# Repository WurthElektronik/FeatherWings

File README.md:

# WE Adafruit FeatherWings

[Würth Elektronik eiSos](https://www.we-online.de/web/en/wuerth_elektronik/start.php) presents, a range of FeatherWing development boards that are **open source** and **fully compatible** with the **Feather form factor**. Through these development boards WE brings a range of wireless connectivity modules, sensors and power modules to the Feather ecosystem.

[Adafruit Feather](https://www.adafruit.com/feather) is a complete line of development boards from [Adafruit](https://www.adafruit.com/) and other developers that are both standalone and stackable. They're able to be powered by [LiPo batteries](https://en.wikipedia.org/wiki/Lithium_polymer_battery) for on-the-go use or by their [micro-USB](https://www.we-online.de/katalog/de/em/connectors/input_output_connectors/wr-com) or their [USB-C](https://www.we-online.com/de/components/products/WR-COM_USB_20_TYPE_C_RECEPTACLE_HORIZONTAL_SMT) plugs for line-powered projects. Feathers are flexible, portable, and as light as their namesake.

[FeatherWings](https://learn.adafruit.com/adafruit-feather/featherwings) are stacking boards and add functionality and room for prototyping. At its core, the Adafruit Feather is a complete ecosystem of products - and the best way to get your project flying.

Supercharge your prototyping for easy and fast solution testing.
Start by checking our [quick start section](#Quick-start-guide).

| Image    | Description |
| -------- | ----------- |
| | [**Proteus-III BLE FeatherWing** (not available as a standalone product)](/Setebos-I_FeatherWing/)<ul><li>Bluetooth® Low Energy 5.1 module<li>Nano SIM size<li>2 MBit PHY and Coded PHY (long range)<li>Connect to any smart device with an app. <br/> <br/> Note: this Feather is replaced by Setebos-I Feather with selectable radio protocol (either Proteus-III Bluetooth LE or Thyone-I)</ul> |
| | [**Adrastea-I FeatherWing** (2615039336001)](/AdrasteaFeatherWing) <ul> <li>LTE-Cat.M/LTE-Cat.NB-IoT<li>AIntegrated GNSS<li>Integrated User MCU<li>Secure IoT Connectivity using MQTT, LWM2M<br/> Note: This board can be used as a featherWing or as a standalone Feather.</ul> |
| | [**Sensor FeatherWing** (2501000201291)](/SensorFeatherWing) <ul> <li>Acceleration (WSEN-ITDS)<li>Absolute Pressure (WSEN-PADS)<li>Temperature (WSEN-TIDS)<li>Humidity (WSEN-HIDS)<li>[Sparkfun QWIIC® Connect System](https://www.sparkfun.com/qwiic) to connect additional peripherals <br/> <br/> Note: this FeatherWing will be updated with new sensors in the future.</ul> |
| | [**Calypso WiFi FeatherWing** (2610039025001)](/CalypsoWiFiFeatherWing)<ul><li>2.4 GHz WiFi-Connectivity <li>Easy and secure connection to Smart Devices<li>Out-of-the-box support to applications like HTTP(S), MQTT(S) <li>AT-style command interface </ul> |
| | [**Daphnis-I LoRaWAN® FeatherWing** (2610039025001)](/DaphnisILoRaWANFeatherWing/)<ul><li> LoRaWAN® and P2P Connectivity <li>LoRaWAN® 1.0.4 (Class A/B/C)<li>Out-of-the-box support to The Things Network <li>AT-style command interface </ul> |
| | [**Thyone-I Wireless FeatherWing** (2611059021001)](/Setebos-I_FeatherWing/)<ul><li>2.4 GHz Proprietary radio Module<li>Easy build up networks<li>Connect to Thyone modules or USB-Stick.<br/> Note: this Feather is replaced by Setebos-I Feather with selectable radio protocol (either Proteus-III Bluetooth LE or Thyone-I).</ul> |
|| [**ICLED FeatherWing** (150015)](/ICLEDFeatherWing) <ul> <li>IC LED: 1312020030000 (WL-ICLED)<li>Power supply via USB-C: 5V @3A<li>Usable with 1.8V logic controllers outside FeatherWing-standard <br/> </ul>|
| | [**MagI³C Power FeatherWing** (2601157100001)](/MagI3CPowerFeatherWing)<ul><li>5 V and 3.3 V power supply<li>Using a range of input voltages (5 V, 9 V, 12 V, 15 V, 18 V and 24 V industrial rails)</ul> |
| | [**Serial Bridge FeatherWing** (2601167101001)](/SerialFeatherWing)<ul><li>RS232/RS485 to UART bridge<li>Retrofit legacy devices with modern Wireless connectivity</ul> |
| | Connect any **Adafruit Feather Microcontroller** <br>(e.g. [Adafruit Feather M0 Express](https://www.adafruit.com/product/3403) or [Adafruit Feather M4 Express](https://www.adafruit.com/product/3857))<ul><li>Request sensor data<li>Transfer data to RF-Module<li>Set the IC LED display<li>Examples available on Github<li>Source code available on Github</ul> |

## Quick start guide

**Read this documentation!**

This step-by-step description will guide you through the setup process for taking WE FeatherWings into operation  and help avoid the most common mistakes.

### Hardware requirements

1. Adafruit Feather M0 - FeatherWings are stackable, add-on boards that bring additional functionality to any Feather board. The current repository contains software developed on the [Adafruit Feather M0 express](https://www.adafruit.com/product/3403).

>**Note**: The WE FeatherWings can only be operated in combination with a Feather. Please use the Feather M0 express for the quick start examples.

2. WE FeatherWing - Please choose the FeatherWing of interest or a combination of FeatherWings and stack it on to the Feather.

3. Stable power supply - Please ensure that the boards are powered using a clean and stable power supply. The following input options are available,
- **USB** interface on the M0 Feather.
>**Note**: Use this option for the quick start examples. The USB interface will also be used to upload the example code to the microcontroller.

- **LiPo** - For low power applications, it is also possible to connect a LiPo battery. Please ensure that the battery can deliver sufficient current at the desired voltage for the combination of boards used.

- [**MagI³C Power FeatherWing** (2601157100001)](/MagI3CPowerFeatherWing) - Stack on this WE FeatherWing to use a range of input voltages (5 V, 9 V, 12 V, 15 V, 18 V and 24 V industrial rails).

- [**IC LED FeatherWing** (1500015)](/ICLEDFeatherWing) via the included USB-C interface - By soldering a 0 &Omega; resistor on R8 it is possible to connect VDD nodes of the IC LED FeatherWing and the Feather M0 board.

4. Computing device with sufficient memory and an internet connection.
>**Note**: The software tools used in the quick start example require up to 2 GB of data storage.

### Software installation
In order to enable ease of prototyping, we use the popular cross platform integrated development environment, [Visual Studio Code](https://code.visualstudio.com/) along with some extensions. The following steps will guide you through the installation process.

1. Download and install **[Visual Studio Code](https://code.visualstudio.com/download)** by following the steps described [here](https://code.visualstudio.com/docs/setup).
>**Note**: If you are in a corporate environment, check with your IT department if you are required to enter proxy settings and credentials inside Visual Studio Code.

2. **Install** the [PlatformIO](https://platformio.org/install/ide?install=vscode) extension for Visual Studio Code.
  - Select **Extensions** in the lower left
  - **Type** platformio in the *Search window* and
  - when PlatformIO IDE extension appears, **press the blue Install button**

> **Note**: Do not close the Visual Studio Code window until PlatformIO is completely installed.
> The installation process may be slow, depending on your computer's speed and network connection. 

3. After the PlatformIO extension has been installed follow the on screen instructions to **restart** Visual Studio Code.

The PlatformIO extension will then be loaded in Visual Studio Code and its icon will appear in the Visual Studio Code menu bar on the left side.

### Running the sample applications

1. **Download documentation and example code** from https://github.com/WurthElektronik/FeatherWings using [git](https://git-scm.com/) ``clone`` https://github.com/WurthElektronik/FeatherWings.git or a simple [zip file](https://github.com/WurthElektronik/FeatherWings/archive/main.zip).

1. This repository contains **the following ready-to-run** applications:
   - [ICLED FeatherWing examples](/ICLEDFeatherWing/software/src) includes several predefined functions to showcase the capabilities of the IC LED FeatherWing. 
   - [Sensor FeatherWing example](/SensorFeatherWing/software) showing the functionality of the Sensor FeatherWing.
   - [Thyone-I Wireless FeatherWing example](/ThyoneWirelessFeatherWing/software) showing the transmit and receive functionality over a 2.4 GHz proprietary wireless link. 
   - [Calypso Wi-Fi FeatherWing example](/CalypsoWiFiFeatherWing/software) showing the Wi-Fi capabilities.
   - [Sensor2Cloud connectivity example](/Sensor2CloudConnectivity) sends data measured using the sensors via Wi-Fi to the Microsoft Azure or Amazon AWS cloud.
   - [Sensor2BLE connectivity example](/Sensor2BLE) uses Bluetooth Low Energy in Role Peripheral to share the Sensor measurement values with a Smart Device. The WE-SensorBLE App is required on the smart device. Requires a Proteus-III compatible radio module, such as available with Setebos-I Feather.
   - [Adrastea Cloud connectivity example](/AdrasteaFeatherWing/software/) showing cloud connectivity via MQTT.
   - [RS232/RS485 to wireless example](/SerialFeatherWing/software/) that shows bridging RS232/RS485 to either Proprietary Wireless link of standard MQTT over Wi-Fi. 
   - [Thyone Wireless Sensors example](/ThyoneWirelessSensors/software/) that shows a sensor node that transmit sensor data over proprietary wireless link.

   - [Sensor data via HTTP example](/SensorDataOnCalypsoWebsite/) shows a demo to display sensor data on a webpage using RestAPIs.  

> **Note**: For more details on each board and workspace, please click on the links above.

3. **Open workspace file** for the case you want to test.

Choose the workspace you would like to work with based on your preferences.

After selecting the workspace, the workspace will appear in your Visual Studio Code and PlatformIO will recognize it as its project. In this quick start guide we will use the simple SensorFeatherWing workspace.

1. After loading the workspace, connect the set of boards you want to test to the USB port for programming.
For that you will need a combination of at least one WE FeatherWing and one microcontroller Feather board (for more details see table below).

5. Go into the PlatformIO extension and select the **PROJECT TASKS** dropdown list.

6. **Build** the code using the PlatformIO extension and then **Upload** it to the microcontroller. The Upload command will also execute Build before it uploads, but doing it in two steps, first Build then Upload, you will be able to check if the code is correctly built and it prevents uploading erroneous code to the microcontroller.

> **Note**: Wait until PlatformIO rebuilds its indices. This process may be slow, depending on
> your computer's speed and network connection.

7. Press **Monitor** and check the Visual Studio Code **TERMINAL** window for results.

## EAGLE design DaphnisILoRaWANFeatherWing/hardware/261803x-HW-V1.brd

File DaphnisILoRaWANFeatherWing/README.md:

# Daphnis-I FeatherWing
## Introduction
The Würth Elektronik eiSos [**Daphnis-I LoRaWAN® FeatherWing**](https://www.we-online.com/DAPHNIS-I_FEATHERWING_KIT) is a development board that brings long-range, ultra-low-power Sub-GHz connectivity to the Adafruit Feather ecosystem. It features the [**Daphnis-I radio module**](https://www.we-online.com/DAPHNIS-I) (based on the STM32WLE5CCU6 chip), compliant with LoRaWAN® 1.0.4 (Class A/B/C) and proprietary P2P, star, and mesh modes in the EU868 band. 

Measuring just 15 × 16 × 3 mm, the module draws a mere 63.9 nA in deep sleep yet delivers up to +13.4 dBm of RF output for extended range. The AT-style UART interface makes integration with any Feather microcontroller as simple as stacking the boards on top of each other and sending commands — no radio-stack hacks required. 

With open-source [Eagle](https://www.autodesk.com/products/eagle/overview) files for the [Daphnis-I FeatherWing PCB](/hardware/) and Arduino (C/C++) libraries, plus [quick-start example](/software), you’ll be prototyping a secure LoRaWAN® IoT application in minutes.

For full specs and usage, please download the [Daphnis-I FeatherWing user manual](https://www.we-online.com/components/products/manual/2618011181000_UM_Daphnis-I_2618011181000_V1_0_rev1.1.pdf). Feel free to check out our [YouTube channel](https://www.youtube.com/user/WuerthElektronik/videos) for video tutorials, hands-on demos and webinars relating to our products.

## Hardware

### Description
The Würth Elektronik eiSos **Daphnis-I LoRaWAN® FeatherWing** was designed with rapid prototyping in mind. Fully compatible with the Adafruit Feather ecosystem, this FeatherWing allows you to choose your preferred Feather host MCU while seamlessly adding long-range, low-power Sub-GHz connectivity.

### Daphnis-I module (2618011181000)
The **Daphnis-I** module is a compact LoRa® radio solution based on the STM32WLE5CCU6 (Arm® Cortex®-M4 @ 48 MHz with integrated Semtech SX126x transceiver). Its edge-castellated pads, flexible antenna options (50 Ω RF pad or UMRF connector) and AT-style UART command interface make it easy to integrate into any embedded project.

The module supports LoRaWAN® 1.0.4 (Class A/B/C) and proprietary modes (P2P, star, mesh) in the EU868 band, with features like adaptive data rate, join-and-transmit and hardware AES-128 encryption built-in. With deep-sleep currents down to 63.9 nA and up to +13.4 dBm TX power, it’s perfect for battery-powered sensors, asset trackers and remote control nodes.

Whether you need a drop-in replacement for serial links or a secure, cloud-connected IoT endpoint, the Daphnis-I FeatherWing offers a robust, standards-compliant wireless solution for low-power, low-throughput applications.

## Key features
The Daphnis-I module offers a rich set of LoRa®-based features accessible via an easy-to-use AT-style command interface over UART.

| Feature            | Description                                                                                  |
|--------------------|----------------------------------------------------------------------------------------------|
| **Protocols**      | LoRaWAN® 1.0.4 (Class A/B/C), Proprietary LoRa® P2P, star & mesh                              |
| **Frequency band** | EU868 MHz (863 – 870 MHz)                                                                    |
| **Channels**       | Per EU868 channel plan (e.g. 0–7, RX1/RX2)                                                   |
| **TX power**       | +2 to +13.4 dBm selectable                                                                    |
| **RX sensitivity** | –138 dBm (SF12 BW125 kHz)                                                             |
| **Security**       | Hardware AES-128 (LoRaWAN payload encryption), STM32 secure boot & flash protection           |
| **Provisioning**   | OTAA & ABP join modes                                                                        |
| **Interface**      | AT-style commands over LPUART1 (PA2/PA3)                                                     |
| **Power management** | Deep‐sleep current down to 63.9 nA; pin- or timer-wake; LoRaWAN Class B/C support         |
| **I/O**            | 8× GPIOs for user I/O, 2× status LEDs, /RESET, /WAKE_UP, BOOT                                |
| **Antenna**        | 50 Ω RF pad or UMRF connector                                                                |
| **Backup domain**  | VBAT supply for RTC & 32 kHz TCXO                                                             |
| **Typical applications** | Battery-powered sensors, asset trackers, remote controls, mesh nodes                |

### Pinout

#### Feather connector

This is the standard 28-pin Feather header. On the Daphnis-I FeatherWing, only the module reset and the default UART lines are used by the module; an alternate UART pair is available via JP1.

| Pin # | Pin name   | Function                                                         |
|-----:|------------|------------------------------------------------------------------|
| 1    | RESET      | Not connected                                                    |
| 2    | 3V         | +3.3 V supply to the FeatherWing                                 |
| 3    | AREF       | Not connected                                                    |
| 4    | GND        | Ground                                                           |
| 5    | GPIOA0     | Not connected                                                    |
| 6    | GPIOA1     | Not connected                                                    |
| 7    | GPIOA2     | Not connected                                                    |
| 8    | GPIOA3     | Not connected                                                    |
| 9    | GPIO4      | **Daphnis-I RESET** (/RESET)                                     |
| 10   | GPIOA4     | Not connected                                                    |
| 11   | GPIOA5     | Not connected                                                    |
| 12   | GPIOSCK    | Not connected                                                    |
| 13   | GPIOMOSI   | Not connected                                                    |
| 14   | GPIOMISO   | Not connected                                                    |
| 15   | GPIORX     | Alternate UART RX → Daphnis-I LPUTXD1 (via JP1)                  |
| 16   | GPIOTX     | Alternate UART TX ← Daphnis-I LPURXD1 (via JP1)                  |
| 17   | GPIOSDA    | Not connected                                                    |
| 18   | GPIOSCL    | Not connected                                                    |
| 19   | GPIO5      | Not connected                                                    |
| 20   | GPIO6      | Not connected                                                    |
| 21   | GPIO9      | Not connected                                                    |
| 22   | GPIO10     | **Default UART RX** ← Daphnis-I LPURXD1 (module RX ← MCU TX)      |
| 23   | GPIO11     | **Default UART TX** → Daphnis-I LPUTXD1 (module TX → MCU RX)      |
| 24   | GPIO12     | Not connected                                                    |
| 25   | GPIO13     | Not connected                                                    |
| 26   | USB        | +5 V USB input (unused on this board)                            |
| 27   | EN         | Feather enable (tied high internally; no user connection)        |
| 28   | VBAT       | Backup-domain supply (tied to 3.3 V if no external backup used)  |

<br>

#### Jumper 1 - UART pin selection
The 2×3 header **JP1** lets you choose which two MCU pins talk to the Daphnis-I’s LPUART1. Moving the two shunts selects either the **factory-default** mapping or the **alternate** mapping.

| Mapping           | Shunt positions         | Module ↔ MCU connection                           |
|-------------------|-------------------------|---------------------------------------------------|
| **Default** (out-of-box)  | pins 1–3 & 2–4 (top row)   | **LPURXD1** ← **GPIOTX**  <br>  **LPUTXD1** → **GPIORX**  |
| **alternate**      | pins 3–5 & 4–6 (bottom row) | **LPURXD1** ← **GPIO10** (Feather TX)  <br>  **LPUTXD1** → **GPIO11** (Feather RX) |

- **LPURXD1** = module UART RX  
- **LPUTXD1** = module UART TX  
- **GPIOTX/GPIORX** = Daphnis-I default GPIO pair  
- **GPIO10/11** = Feather’s primary Serial1 pins (D10 = TX, D11 = RX)  

By default, the shunts are installed on the **top row**, connecting LPUART1 to the chosen default pins. To use the standard Feather Serial1 (D10/D11), move both shunts to the **bottom row**.  

#### Jumper 2 - Bootloader Mode
The 2×3 header **JP2** lets you enter the Daphnis-I system bootloader and route its bootloader-UART (UTXD1/URXD1) into your Feather MCU. Install the shunts as follows:

| Mode                  | Shunt positions        | Module ↔ MCU connection                                       |
|-----------------------|------------------------|---------------------------------------------------------------|
| **Normal operation**  | *none* (all open)      | BOOT0 ← internal pull-down (run user firmware) <br> UTXD1/URXD1 disconnected |
| **Firmware update**   | 1–2, 3–4 & 5–6         | BOOT0 ← +3.3 V (pull high to enter bootloader) <br> UTXD1 → GPIO11 (RX) <br> URXD1 ← GPIO10 (TX) |

- **BOOT0** = module boot-select pin (PH3)  
- **UTXD1** = module bootloader TX (pin 4 of JP2)  
- **URXD1** = module bootloader RX (pin 6 of JP2)  
- **GPIO10/11** = Feather’s Serial1 TX/RX (D10 → TX, D11 ← RX)  

By default no jumpers are fitted, so your Daphnis-I runs its LoRaWAN® firmware. To flash a new image, install all three shunts, which ties BOOT0 high and routes the module’s bootloader UART into your MCU’s Serial1 port.  

#### Push button S1
This push button is connected to the /RESET pin of the Daphnis-I module. Pressing this button resets the module.

### Schematics

### DISCLAIMER:
THE USE OF THE WÜRTH ELEKTRONIK EISOS DESIGN EXAMPLE / REFERENCE DESIGN IS ENTIRELY AT YOUR OWN RISK. IT IS YOUR SOLE RESPONSIBILITY TO IMPLEMENT THE DESIGN EXAMPLE / REFERENCE DESIGN WITH ALL TECHNICAL AND REGULATORY REQUIREMENTS IN YOUR APPLICATION. IT IS ALSO YOUR RESPONSIBILITY TO VERIFY THE FUNCTION AND PERFORMANCE OF YOUR DESIGN IN YOUR OWN PARTICULAR ENGINEERING AND PRODUCT ENVIRONMENT AND YOU ASSUME THE ENTIRE RISK OF DOING SO OR FAILING TO DO SO. THE WÜRTH ELEKTRONIK EISOS DESIGN EXAMPLE / REFERENCE DESIGN IS PROVIDED ON AN "AS IS" OR "AS AVAILABLE" BASIS, WITHOUT ANY WARRANTIES OF ANY KIND AND WÜRTH ELEKTRONIK EISOS DISCLAIMS ANY WARRANTIES EXPRESS OR IMPLIED, INCLUDING WITHOUT LIMITATION THE MERCHANTABILITY OR FITNESS FOR A PARTICULAR PURPOSE, USAGE OR THE NON-INFRINGEMENT OF THIRD PARTIES’ INTELLECTUAL PROPERTY RIGHTS. NO LICENSE IS GRANTED TO ANY INTELLECTUAL PROPERTY RIGHT BY WÜRTH ELEKTRONIK EISOS OR ANY THIRD PARY. UNDER NO CIRCUMSTANCES SHALL WÜRTH ELEKTRONIK EISOS BE LIABLE FOR DAMAGES INCURRED BY REASON OF OTHER SERVICES OR PRODUCTS RECEIVED THROUGH OR ADVERTISED IN CONNECTION WITH THE WÜRTH ELEKTRONIK EISOS SITE OR THE WÜRTH ELEKTRONIK EISOS DESIGN EXAMPLE / REFERENCE DESIGN. THE WÜRTH ELEKTRONIK EISOS DESIGN EXAMPLE / REFERENCE DESIGN IS SUBJECT TO CHANGE WITHOUT NOTICE.

## Software
You can find two examples for the Daphnis-I LoRaWAN® FeatherWing.

1. Secure connection to a LNS network and further to the cloud can be found in the [software folder](./software).
2. A simple P2P example can be found [here](../DaphnisIP2PFeatherWing/).

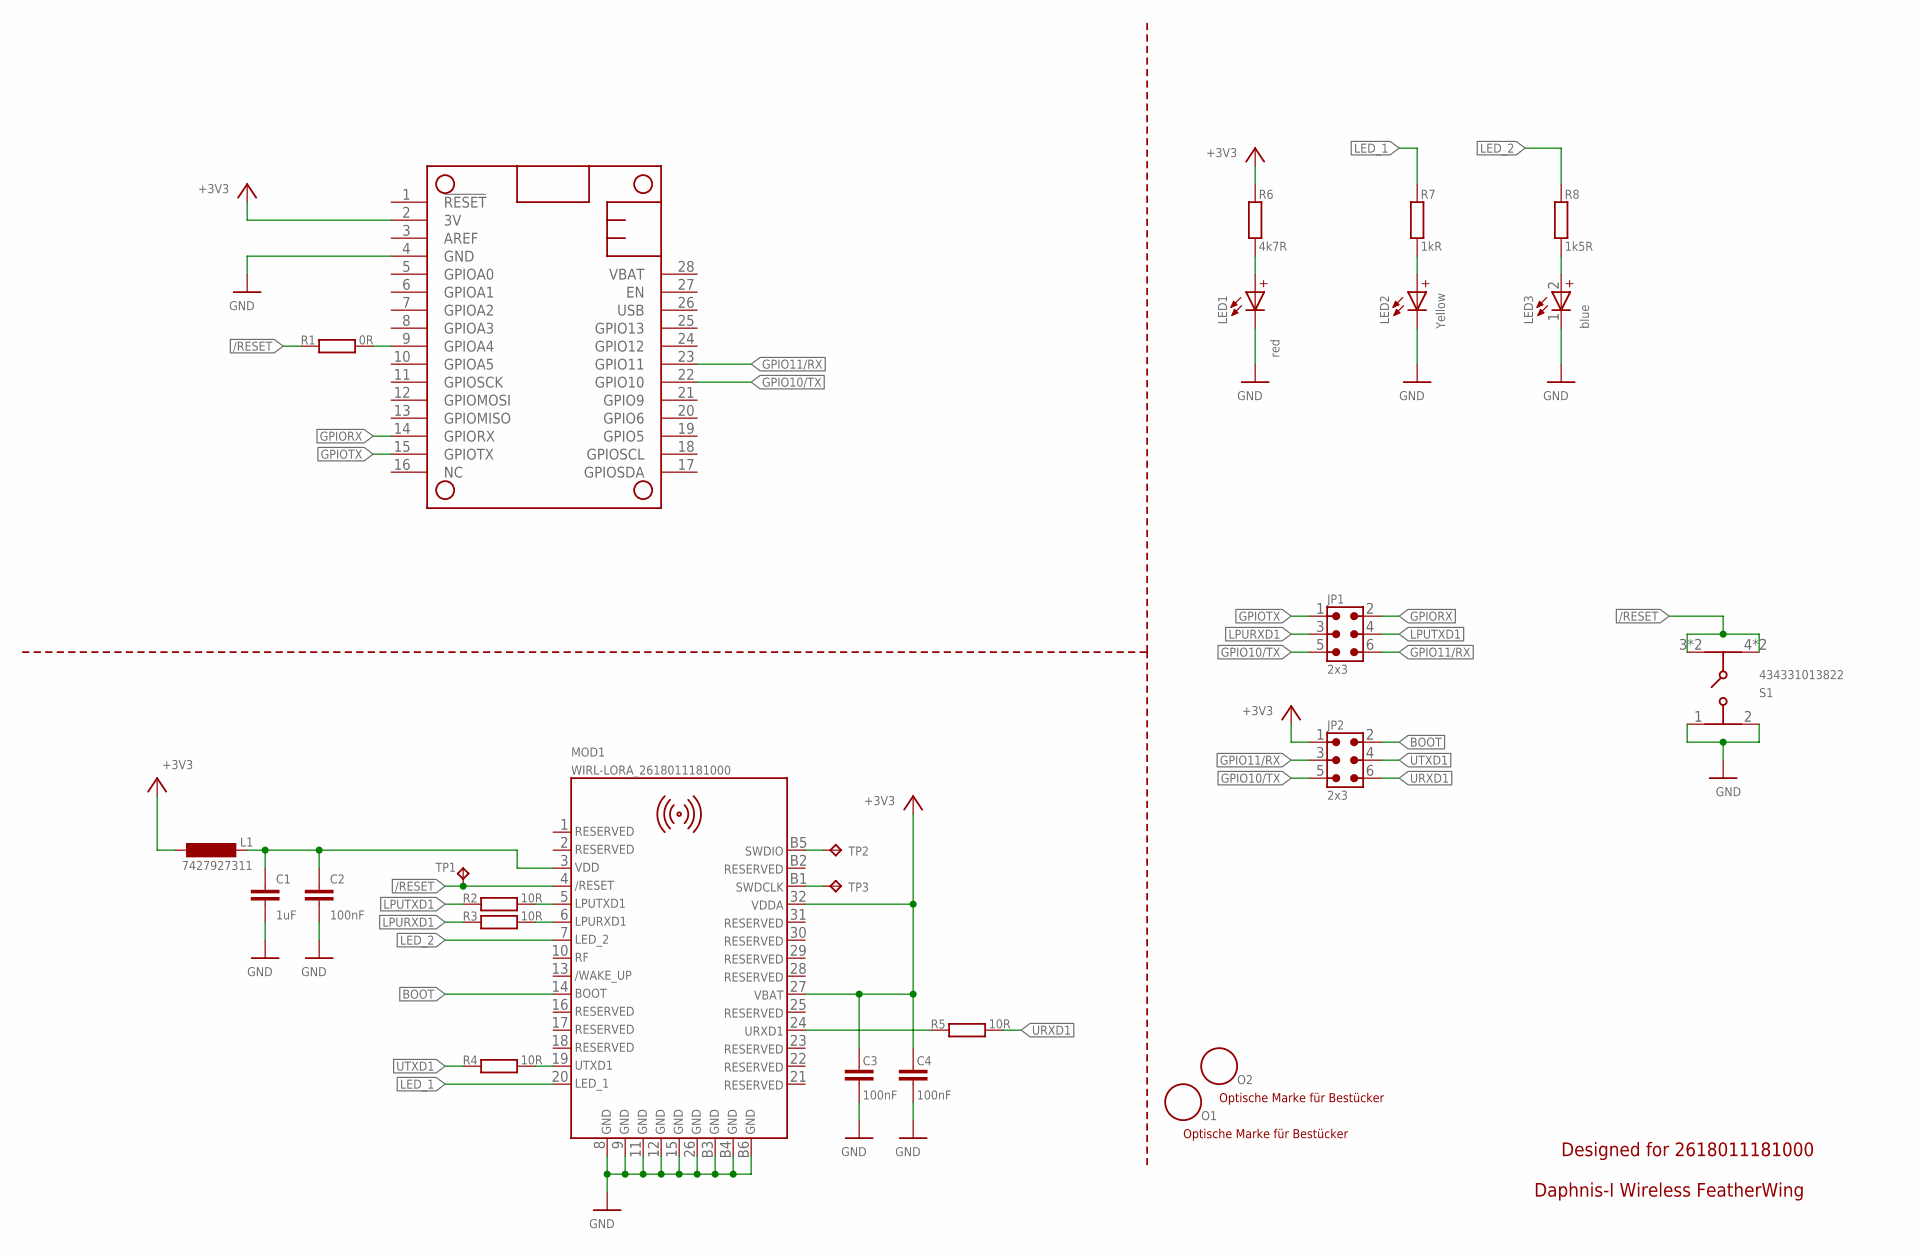
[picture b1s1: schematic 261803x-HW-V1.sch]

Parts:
C1: 1uF; C0402_IPC
C2, C3, C4: 100nF; C0402_IPC
JP1, JP2: 2x3; 61300621121
L1: 7427927311; L0402_WE-MK
LED1: red; WL-SMSW_1204_A
LED2: Yellow; WL-SMSW_1204_A
LED3: blue; WL-SMSW_1204_A
MOD1: WIRL-LORA_2618011181000; WE-FP-8
MS1: header: 1 x 12 & 1 x 16; FEATHERWING
O1, O2: n.m.; OPTISCHE_MARKE
R1: 0R; R0402_IPC
R2, R3, R4, R5: 10R; R0402_IPC
R6: 4k7R; R0402_IPC
R7: 1kR; R0402_IPC
R8: 1k5R; R0402_IPC
S1: 434331013822
TP1, TP2, TP3: TP15R

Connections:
+3V3: C3.1, C4.1, JP2.1, L1.P$2 (2), MOD1.27, MOD1.32, MS1.2 (3V), R6.2
/RESET: MOD1.4, R1.1, S1.3, S1.4, S1.5 (3), S1.6 (4), TP1.P$1
BOOT: JP2.2, MOD1.14
GND: C1.2, C2.2, C3.2, C4.2, LED1.1 (-), LED2.1 (-), LED3.1 (-), MOD1.8, MOD1.9, MOD1.11, MOD1.12, MOD1.15, MOD1.26, MOD1.B3, MOD1.B4, MOD1.B6, MS1.4 (GND), S1.1, S1.2
GPIO10/TX: JP1.5, JP2.5, MS1.22 (GPIO10)
GPIO11/RX: JP1.6, JP2.3, MS1.23 (GPIO11)
GPIORX: JP1.2, MS1.14 (GPIORX)
GPIOTX: JP1.1, MS1.15 (GPIOTX)
LED_1: MOD1.20, R7.2
LED_2: MOD1.7, R8.2
LPURXD1: JP1.3, R3.2
LPUTXD1: JP1.4, R2.1
unnamed: LED1.2 (+), R6.1
unnamed: LED2.2 (+), R7.1
unnamed: LED3.2 (+), R8.1
unnamed: C1.1, C2.1, L1.P$1 (1), MOD1.3
unnamed: MOD1.19, R4.2
unnamed: MOD1.24, R5.1
unnamed: MS1.9 (GPIOA4), R1.2
unnamed: MOD1.6, R3.1
unnamed: MOD1.5, R2.2
SWDCLK: MOD1.B1, TP3.P$1
SWDIO: MOD1.B5, TP2.P$1
URXD1: JP2.6, R5.2
UTXD1: JP2.4, R4.1

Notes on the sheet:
Daphnis-I Wireless FeatherWing
Designed for 2618011181000

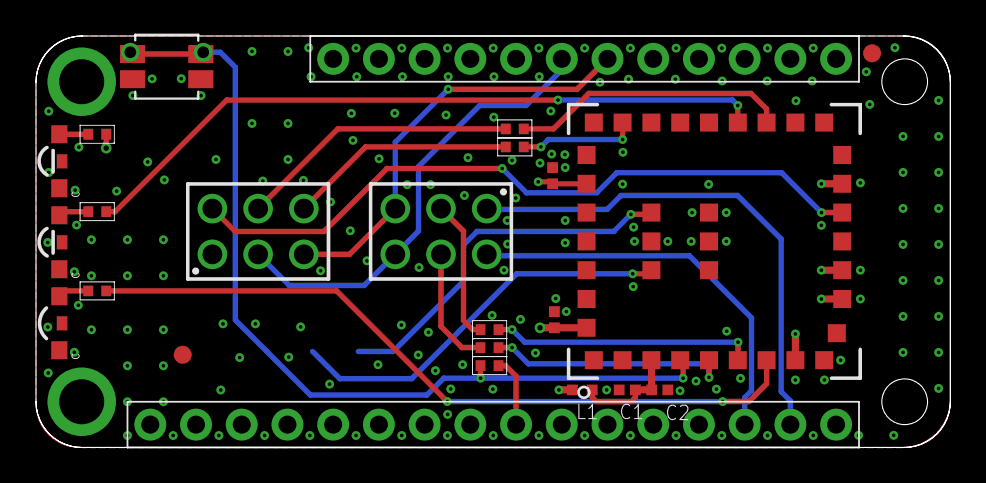
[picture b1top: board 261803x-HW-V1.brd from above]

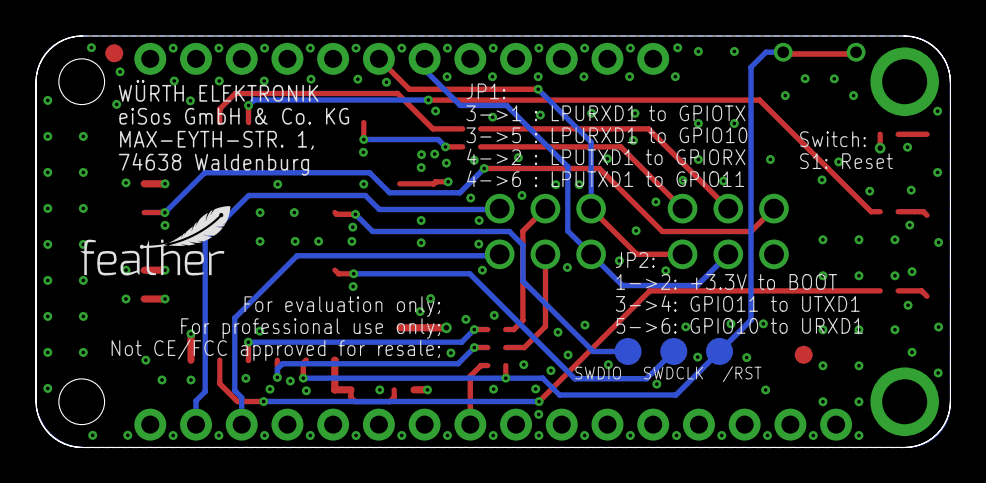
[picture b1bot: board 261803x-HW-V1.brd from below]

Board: 4 copper layers, 50.8 x 22.9 mm, 27 parts (4 on the bottom side), 25 nets.

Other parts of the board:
U$3: FEATHER_8MM

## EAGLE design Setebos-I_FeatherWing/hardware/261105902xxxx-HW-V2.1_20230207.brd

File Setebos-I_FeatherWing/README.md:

# Setebos-I Wireless FeatherWing

## Introduction

The Würth Elektronik eiSos [Setebos-I Wireless FeatherWing](https://www.we-online.de/katalog/en/SETEBOS-I_FeatherWing) is a development board that offers a combination of two different radio protocols in the 2.4 GHz ISM band. It is fully compatible to the popular [Adafruit](https://www.adafruit.com/) [Feather line](https://www.adafruit.com/feather) of development boards and consists if the following primary components:

* [**Setebos-I**](https://www.we-online.de/katalog/SETEBOS-I) [(2611011024020)](https://www.we-online.de/katalog/datasheet/2611011024020.pdf) - 2.4 GHz proprietary radio module
* [**ATECC608B-TNGTLS**](https://www.microchip.com/en-us/product/ATECC608B) - Secure element from Microchip Technologies

The Setebos-I Wireless FeatherWing can be configured to operate in one of the following modes:

* Bluetooth® LE 5.1 functionality based on the [**Proteus-III**](https://www.we-online.de/katalog/PROTEUS-III) radio module (default)
* Proprietary 2.4GHz radio based on [**Thyone-I**](https://www.we-online.de/katalog/THYONE-I) radio module. The secure element can
be used to secure the radio link with authentication and end-to-end encryption.

>[!NOTE] 
>The Setebos-I Wireless FeatherWing is the direct replacement for the Thyone-I
Wireless FeatherWing (2611059021001) and adds the Bluetooth® LE functionality.

>[!NOTE]
>The Setebos-I Wireless FeatherWing is configured to start with the Proteus-III
Bluetooth® LE 5.1 functionality by default.

>[!NOTE]
>For using the proprietary radio protocol based on Thyone-I, the solder bridge
jumper SJ4 shall be shorted and pin 5 of the Feather connector shall be pulled
to 3.3 V.

The Setebos-I module has an UART interface and the secure element an I<sup>2</sup>C interface and hence can be connected to any of the Feather microcontroller boards. The available [Arduino](https://www.arduino.cc/) (C/C++) drivers and examples (see [software folder](software)) make it easy to build a prototype to kick-start the application development.

The Setebos-I Wireless FeatherWing was designed with rapid application prototyping in mind.
Being fully compatible with the [Adafruit ecosystem](https://www.adafruit.com/), this[FeatherWing](https://www.adafruit.com/feather) allows the user the flexibility to choose the preferred host microcontroller. The inherent modularity of the ecosystem allows the FeatherWing to be easily integrated into any project.

This repository contains the [Eagle](https://www.autodesk.com/products/eagle/overview) design files for the Setebos-I Wireless FeatherWing [PCB](hardware) as well as examples software examples for each mode of operation.

For more information, please download the [Setebos-I wireless FeatherWing user manual](docs/SetebosWirelessFeatherWing.pdf). Feel free to check our [YouTube channel](https://www.youtube.com/user/WuerthElektronik/videos) for video tutorials, hands-ons and webinars relating to our products.

### Secure Element

The Setebos-I Wireless FeatherWing contains a [ATECC608B-TNGTLS](https://www.microchip.com/wwwproducts/en/ATECC608B) Microchip secure element. The ATECC608B-TNGTLS is a pre-provisioned variant of the ATECC608B secure element from Microchip Technologies. The device is configured to make the secure element suitable to some of the most common use cases for IoT applications. It offers a rich set of cryptographic features like key agreement using **ECDH**, **sign-verify mechanism**, and **encryption/decryption** over easily accessible I<sup>2</sup>C interface. Its tiny form factor and low power consumption makes it suitable for a wide variety of battery-driven applications.

## Software

This repository provides the following examples for the Setebos-I Wireless FeatherWing:

* The example for Bluetooth® LE 5.1 functionality can be found [here](../ProteusIIIFeatherWing/software/).
* The example for the Proprietary 2.4GHz radio can be found [here](../ThyoneWirelessFeatherWing/software/) 
* The example to transmit sensor data over Bluetooth® LE 5.1 can be found [here](../Sensor2BLE/)
* The example to transmit sensor data over Proprietary 2.4GHz radio can be found [here](../ThyoneWirelessSensors/software/)

## Hardware

### Description

The Setebos-I is a radio module for wireless communication between devices such as control systems, remote controls, sensor nodes etc. Operating in the globally available 2.4 GHz license free band, it combines two radio standards in a single hardware platform. The Setebos-I can be configured to work with either Bluetooth® LE, or with WE-ProWare radio stack.

* When selecting the Bluetooth® LE standard, the Setebos-I acts as a [Proteus-III](https://www.we-online.de/katalog/PROTEUS-III) radio module.
* When selecting the WE-ProWare radio stack, the Setebos-I acts as a [Thyone-I](https://www.we-online.de/katalog/THYONE-I) radio module.

Small dimensions (8 x 12 mm) comparable to a nano-sim card including an on-board PCB antenna make Setebos-I ideal for small form factor design. The Setebos-I interfaces the host system via serial UART.

### Key features

The Setebos-I offers a wide range of configurable features to suit even the most sophisticated application design. From low power long range to line-powered high throughput, the Setebos-I can be configured to cover a wide range of applications.

* **Extremely small dimensions**: Owing to its small size (8 x 12 mm) the module can be easily designed-in to compact end devices.
* **Energy efficient**: The Setebos-I has extremely low current consumption especially in sleep mode(< 0.4 μ A) making it suitable for battery driven applications.
* **Globally available 2.4 GHz band**: The Setebos-I operates in the 2.4 GHz license free band that allows global deployment of the end-device.
* **Smart antenna selection**: The Setebos-I offers a choice of using the on-board PCB antenna for compact designs or connecting an external antenna for application that require long range.
* **Configurable radio profiles**: The module can be configured to operate in 125, 500, 1000 and 2000 kbit/s radio profiles offering the versatility of long range or high throughput.
* **Fast serial interface**: The Setebos-I offers a UART-interface to communicate with a host using a user-defined baud rate of up to 1 Mbit/s.
* **Embedded security on-module**: The secure bootloader on the module verifies the image signature on boot-up offering tamper protection. The module also supports hardware accelerated end-to-end encryption.
* **Additional Local/Remote GPIOs**: The Setebos-I firmware allows configuration and control of free digital I/O pins on the module via serial or radio interface.
* **Transparent mode**: A transparent mode is available out-of-the-box enabling easy serial cable replacement.

Further details about the Setebos-I radio module can be found under [we-online.de/katalog/en/Setebos-I](https://www.we-online.de/katalog/en/Setebos-I).

### Pinouts

#### Feather Connector
This is the standard set of connectors that is used across the Feather ecosystem. The table below describes the functions of each of the 28 pins as applicable to this FeatherWing.

| Pin number | Pin name | Function |
| ------- | ------- |----------------|
|   1          | <span style="text-decoration:overline">RST</span> | Not connected|
|    2          | 3V3| 3.3 V power supply|
|    3          | AREF| Not connected|
|    4          | GND| Ground|
|    5          | A0| (Optional) Module’s pin RPS(B1) via solder bridge SJ4|
|    6          | A1| Not connected|
|    7          | A2| Not connected|
|    8          | A3| (Optional) Module’s pin MODE_1 via solder bridge SJ2|
|    9          | A4| Not connected|
|    10         | A5| Not connected|
|    11         | SCK| Not connected|
|    12         | MOSI| Not connected|
|    13         | MISO| Not connected|
|    14         | U0RX|  (Optional) Module’s UTXD pin via R18|
|    15         | U0TX| (Optional) Module’s URXD pin via R17|
|    16         | NC| Not connected|

| Pin number | Pin name | Function |
| ------- | ------- |----------------|
|    17         | SDA|I<sup>2</sup>C SDA to secure element|
|    18         | SCL|I<sup>2</sup>C SCL to secure element|
|    19         | 5| (Optional) Module’s pin /CTS via solder bridge SJ6|
|    20         | 6| (Optional) Module’s pin /RTS via solder bridge SJ5|
|    21         | 9|  (Optional) Module’s pin WAKE_UP via solder bridge SJ1|
|    22         | U1TX| Module’s pin URXD via R13 |
|    23         | U1RX| Module’s pin UTXD via R14|
|    24         | 12| Not connected|
|    25         | 13| (Optional) Push button S2 via solder bridge SJ3|
|    26         | 5V| Not connected|
|    27         | EN| Not connected|
|    28         | VBAT| Not connected| 

#### CON2

Connector CON2 is a single connector that enables connection to BOOT pin via a standard jumper cable.

|CON2 | Function |
| ------- | ------- |
|- | Direct connection to module's BOOT pin|

### Jumpers and solder briges

#### Solder bridges
These solder bridge jumpers enable optional connection between the pins of the radio module
and the switch S2 to the pins on the Feather connector. Table below shows the functionality and the default state of each solder bridge.

|SJ | Function  | PCB location |Jumper set (Default) |
| ------- | ------- |------------|----------------|
| 1	| WAKE_UP to GPIO9 |	Top |No |
| 2	| MODE_1 to GPIOA3 |	Top |No |
| 3	| Switch S2 to GPIO13 |	Top |Yes|
| 4	| RPS(B1) to GPIO0 |	Bottom |No|
| 5	| /RTS to GPIOA6 |	Bottom |No|
| 6	|/CTS to GPIO5|	Bottom |No|

>[!NOTE] 
> The RPS pin shall be set to switch between Bluetooth® and proprietary radio using the GPIOA3
protocol.

#### Jumper JP2
The standard I<sup>2</sup>C interface requires the SCL and SDA lines to be pulled up with resistors. These jumpers can be removed in cases where the pull-ups already exist on the I<sup>2</sup>C bus. 

| Pin connection | Function  | Jumper set (Default) |
| ------- | ------- |----------------|
|    1,2|	Connect  I<sup>2</sup>C SCL line to a 4.7 k<span>&#8486;</span> Pull up resistor|	Yes|
|    3,4|	Connect  I<sup>2</sup>C SDA line to a 4.7 k<span>&#8486;</span> Pull up resistor|	Yes|

#### Push button S1
This push button is connected to the /RESET pin of the Setebos-I module. Pressing this button resets the module.

#### Push button S2
S2 is a general purpose push button which is connected to GPIO 13 when a jumper is set between pins 5 and 6 of JP1.

### Schematics

### DISCLAIMER:
THE USE OF THE WÜRTH ELEKTRONIK EISOS DESIGN EXAMPLE / REFERENCE DESIGN IS ENTIRELY AT YOUR OWN RISK. IT IS YOUR SOLE RESPONSIBILITY TO IMPLEMENT THE DESIGN EXAMPLE / REFERENCE DESIGN WITH ALL TECHNICAL AND REGULATORY REQUIREMENTS IN YOUR APPLICATION. IT IS ALSO YOUR RESPONSIBILITY TO VERIFY THE FUNCTION AND PERFORMANCE OF YOUR DESIGN IN YOUR OWN PARTICULAR ENGINEERING AND PRODUCT ENVIRONMENT AND YOU ASSUME THE ENTIRE RISK OF DOING SO OR FAILING TO DO SO. THE WÜRTH ELEKTRONIK EISOS DESIGN EXAMPLE / REFERENCE DESIGN IS PROVIDED ON AN "AS IS" OR "AS AVAILABLE" BASIS, WITHOUT ANY WARRANTIES OF ANY KIND AND WÜRTH ELEKTRONIK EISOS DISCLAIMS ANY WARRANTIES EXPRESS OR IMPLIED, INCLUDING WITHOUT LIMITATION THE MERCHANTABILITY OR FITNESS FOR A PARTICULAR PURPOSE, USAGE OR THE NON-INFRINGEMENT OF THIRD PARTIES’ INTELLECTUAL PROPERTY RIGHTS. NO LICENSE IS GRANTED TO ANY INTELLECTUAL PROPERTY RIGHT BY WÜRTH ELEKTRONIK EISOS OR ANY THIRD PARY. UNDER NO CIRCUMSTANCES SHALL WÜRTH ELEKTRONIK EISOS BE LIABLE FOR DAMAGES INCURRED BY REASON OF OTHER SERVICES OR PRODUCTS RECEIVED THROUGH OR ADVERTISED IN CONNECTION WITH THE WÜRTH ELEKTRONIK EISOS SITE OR THE WÜRTH ELEKTRONIK EISOS DESIGN EXAMPLE / REFERENCE DESIGN. THE WÜRTH ELEKTRONIK EISOS DESIGN EXAMPLE / REFERENCE DESIGN IS SUBJECT TO CHANGE WITHOUT NOTICE.

## Software

Setebos-I Wireless FeatherWing **software examples** can be found in the [software folder](software).

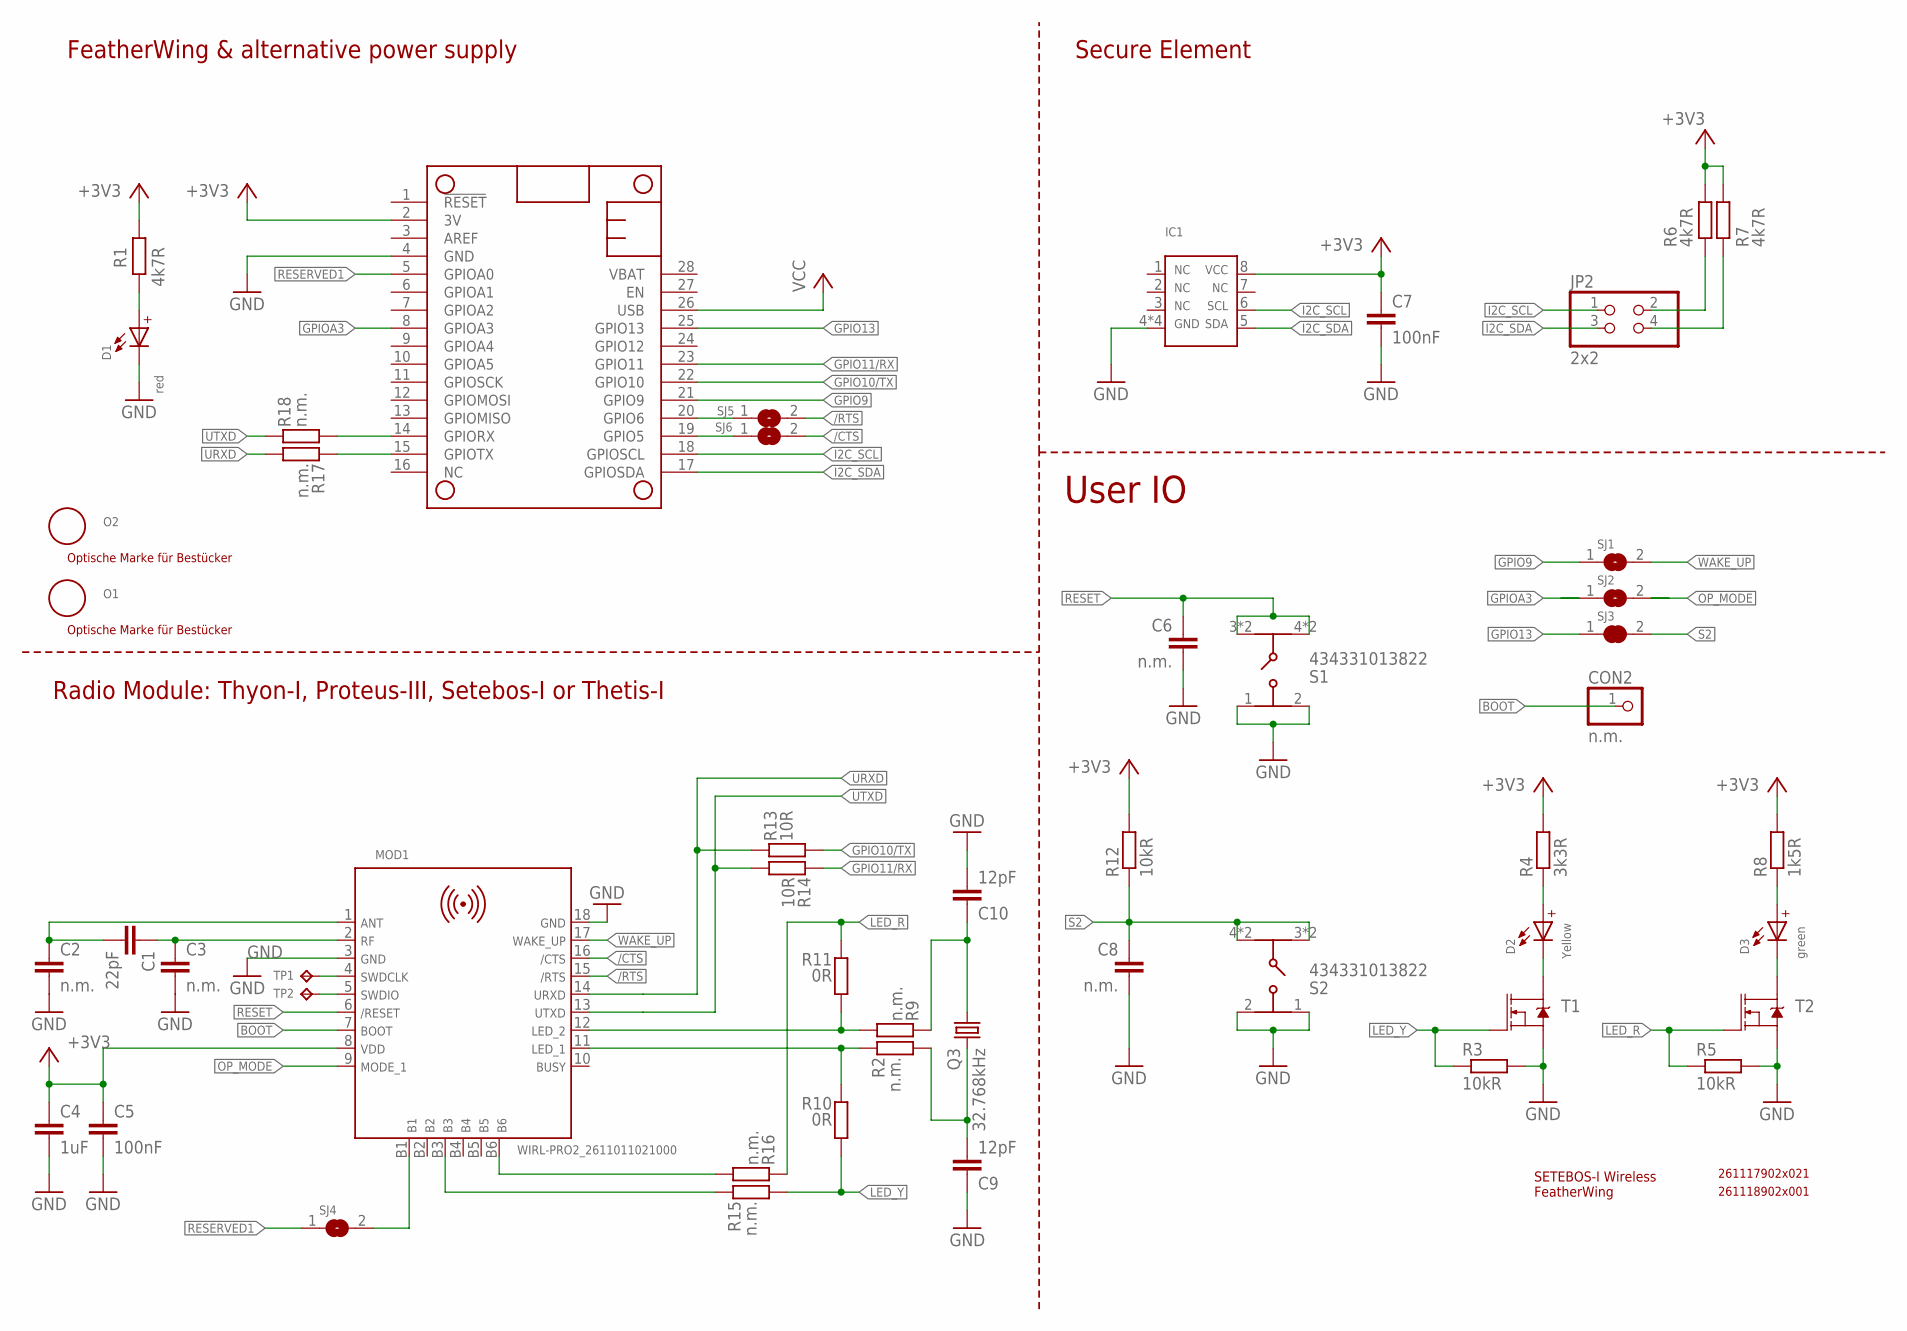
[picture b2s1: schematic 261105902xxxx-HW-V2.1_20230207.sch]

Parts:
C1: 22pF; C0402_IPC
C2, C3, C6, C8: n.m.; C0402_IPC
C4: 1uF; C0402_IPC
C5, C7: 100nF; C0402_IPC
C9, C10: 12pF; C0402_IPC
CON2: n.m.; 1X01/R
D1: red; WL-SMSW_1204_A
D2: Yellow; WL-SMSW_1204_A
D3: green; WL-SMSW_1204_A
IC1: ATECC608B; UDFN-8
JP2: 2x2; 2X02
MOD1: WIRL-PRO2_2611011021000
MS1: header: 1 x 12 & 1 x 16; FEATHERWING
O1, O2: n.m.; OPTISCHE_MARKE
Q3: 32.768kHz; 3216
R1, R6, R7: 4k7R; R0402_IPC
R2, R9, R15, R16, R17, R18: n.m.; R0402_IPC
R3, R5, R12: 10kR; R0402_IPC
R4: 3k3R; R0402_IPC
R8: 1k5R; R0402_IPC
R10, R11: 0R; R0402_IPC
R13, R14: 10R; R0402_IPC
S1, S2: 434331013822
SJ1, SJ2, SJ4, SJ5, SJ6: SJ
SJ3: SJ_SHUNTD; SJ_D
T1, T2: MOSFET-NCH-BSS138; SOT23-3
TP1, TP2: TP15R

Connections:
+3V3: C4.1, C5.1, C7.1, IC1.8 (VCC), MOD1.8 (VDD), MS1.2 (3V), R1.2, R4.2, R6.2, R7.2, R8.2, R12.2
/CTS: MOD1.16 (P0.12/!CTS), SJ6.2
/RTS: MOD1.15 (P0.11/!RTS), SJ5.2
ANT: C1.2, C2.1, MOD1.1 (ANT_PAD)
BOOT: CON2.1, MOD1.7 (P0.02/BOOT)
GND: C2.2, C3.2, C4.2, C5.2, C6.2, C7.2, C8.2, C9.1, C10.2, D1.1 (-), IC1.4 (GND), IC1.P$1 (GND), IC1.P$2 (GND), IC1.THERMAL_PAD (GND), MOD1.3 (GND), MOD1.18 (GND), MS1.4 (GND), R3.2, R5.2, S1.1, S1.2, S2.1, S2.2, T1.2 (S), T2.2 (S)
GPIO9: MS1.21 (GPIO9), SJ1.1
GPIO10/TX: MS1.22 (GPIO10), R13.2
GPIO11/RX: MS1.23 (GPIO11), R14.1
GPIO13: MS1.25 (GPIO13), SJ3.1
GPIOA3: MS1.8 (GPIOA3), SJ2.1
I2C_SCL: IC1.6 (SCL), JP2.1, MS1.18 (GPIOSCL)
I2C_SDA: IC1.5 (SDA), JP2.3, MS1.17 (GPIOSDA)
LED_R: R5.1, R11.1, R16.1, T2.1 (G)
LED_Y: R3.1, R10.2, R15.2, T1.1 (G)
unnamed: D1.2 (+), R1.1
unnamed: D2.2 (+), R4.1
unnamed: D2.1 (-), T1.3 (D)
unnamed: D3.2 (+), R8.1
unnamed: D3.1 (-), T2.3 (D)
unnamed: JP2.2, R6.1
unnamed: JP2.4, R7.1
unnamed: MOD1.B1, SJ4.2
unnamed: MOD1.12 (P0.01/LED_2), R9.2, R11.2
unnamed: MOD1.11 (P0.00/LED_1), R2.1, R10.1
unnamed: C9.2, Q3.2, R2.2
unnamed: C10.1, Q3.1, R9.1
unnamed: MS1.20 (GPIO6), SJ5.1
unnamed: MS1.19 (GPIO5), SJ6.1
unnamed: MOD1.B3, R15.1
unnamed: MOD1.B6, R16.2
unnamed: MS1.14 (GPIORX), R18.2
unnamed: MS1.15 (GPIOTX), R17.1
OP_MODE: MOD1.9 (P0.19/MODE_1), SJ2.2
RESERVED1: MS1.5 (GPIOA0), SJ4.1
RESET: C6.1, MOD1.6 (P0.18/RESET), S1.3, S1.4, S1.5 (3), S1.6 (4)
RF: C1.1, C3.1, MOD1.2 (RF)
S2: C8.1, R12.1, S2.3, S2.4, S2.5 (3), S2.6 (4), SJ3.2
SWDCLK: MOD1.4 (SWDCLK), TP1.P$1
SWDIO: MOD1.5 (SWDIO), TP2.P$1
URXD: MOD1.14 (P1.09/URXD), R13.1, R17.2
UTXD: MOD1.13 (P1.08/UTXD), R14.2, R18.1
VCC: MS1.26 (USB)
WAKE_UP: MOD1.17 (P0.03/WAKE_UP), SJ1.2

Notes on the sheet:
SETEBOS-I Wireless FeatherWing
User IO
Secure Element
Radio Module: Thyon-I, Proteus-III, Setebos-I or Thetis-I
FeatherWing & alternative power supply
261117902x021
261118902x001

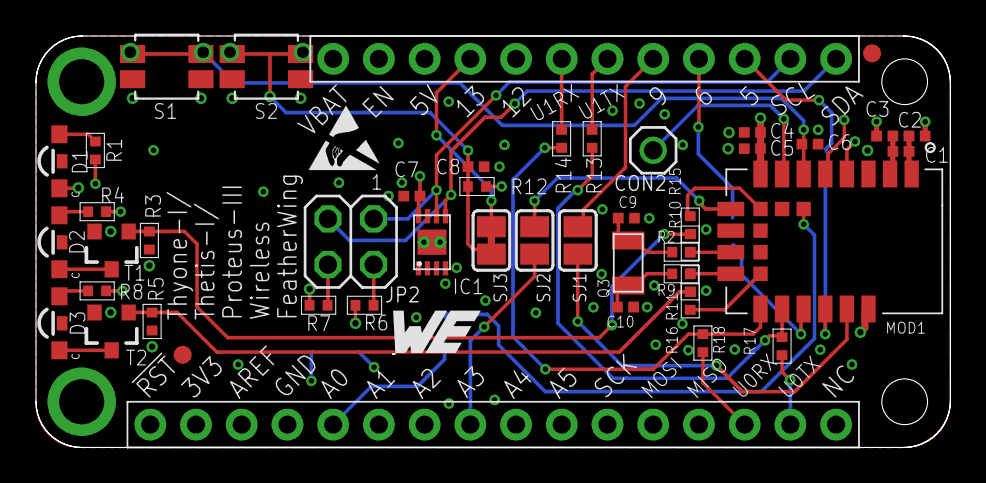
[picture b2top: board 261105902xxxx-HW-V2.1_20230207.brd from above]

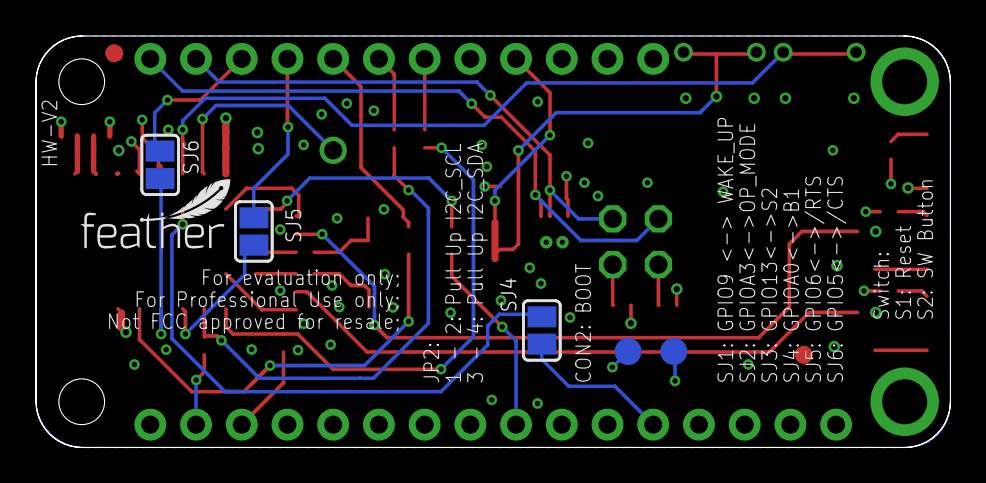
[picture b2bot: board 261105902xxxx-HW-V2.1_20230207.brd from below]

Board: 4 copper layers, 50.8 x 22.9 mm, 54 parts (6 on the bottom side), 43 nets.

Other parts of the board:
U$1: ESD_4MM
U$2: WE-8MM_TNAME
U$3: FEATHER_8MM

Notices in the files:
parts and their libraries:
155124YS73200A_Eagle_WL-SMSW_rev20a: Copyright: Würth Elektronik
SparkFun-DiscreteSemi: Licensing: Creative Commons ShareAlike 4.0 International - https://creativecommons.org/licenses/by-sa/4.0
COPYRIGHT: Copyright (C) 2021 Ultra Librarian. All rights reserved.
